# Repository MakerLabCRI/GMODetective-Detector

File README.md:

# GMODetective-Detector

DIY fluorescence detector for the [GMO Detective project](https://gmodetective.com/)

## BOM

8x C503B-BAN-CZ0A0451 [mouser](https://www.mouser.fr/ProductDetail/Cree-Inc/C503B-BAN-CZ0A0451?qs=%2Fha2pyFaduidizlAeORLOPChSupn8qVQ9Kn4bl13zJ7nUG9%252B2UeDbT0K%252B9FgAF1f)

8x 68 ohm resistor [mouser](https://www.mouser.fr/ProductDetail/Yageo/CFR-25JT-52-68R?qs=%2Fha2pyFaduip15hodXcAQzG82qC8UTcP%2FVcFQd8KsgKmaA7VFXCJAQ%3D%3D)

1x 10uF electrolytic capacitor [mouser](https://www.mouser.fr/ProductDetail/Panasonic/ECA-1JM100B?qs=%2Fha2pyFadugf96c9oovEvKSc4mhyX5s0jUH4ND99LTDADYv5TkhqzA%3D%3D)

1x Fuse 500ma RXEF050 [mouser](https://www.mouser.fr/ProductDetail/Littelfuse/RXEF050?qs=k5V78Jg%2Feq7BserVMEB6DA%3D%3D)

1x micro USB 2P with 90° pins [Taobao](https://item.taobao.com/item.htm?spm=a230r.1.14.68.312b6bc3MnUb4G&id=597273597165&ns=1&abbucket=19#detail)
[Aliexpress](https://fr.aliexpress.com/item/4000049679173.html?spm=a2g0o.productlist.0.0.6fd1f912MCE4d2&algo_pvid=a3873bf6-c53e-42d9-8363-89ecb1d975f8&algo_expid=a3873bf6-c53e-42d9-8363-89ecb1d975f8-4&btsid=0b0a182b16071189178941562e2389&ws_ab_test=searchweb0_0,searchweb201602_,searchweb201603)
[Aliexpress (90 ° version color B or D)](https://aliexpress.com/item/4001293555150.html)
[Aliexpress (90° version color A or C)](https://fr.aliexpress.com/item/1005001515820458.html)

## 3D Model of PCB

## 3d printable frame

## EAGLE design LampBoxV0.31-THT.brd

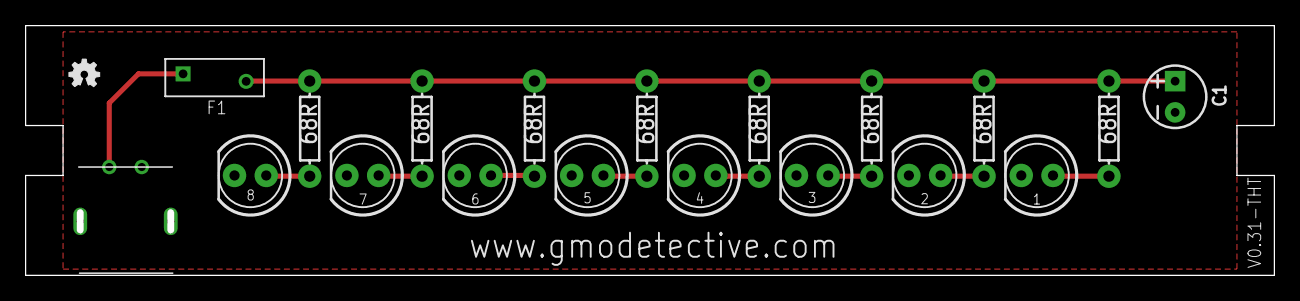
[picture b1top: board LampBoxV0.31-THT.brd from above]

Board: 2 copper layers, 100.0 x 20.0 mm, 22 parts (1 on the bottom side), 11 nets.

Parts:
1, 2, 3, 4, 5, 6, 7, 8: LED_5MM
C1: 10UF-POLARGMODETECTOR; CPOL-RADIAL-2.5MM-5MM
F1: LITTELFUSE_RXEF050LITTELFUSE_RXEF050_0_0; LITTELFUSE_RXEF050_0
LOGO1: OSHW-LOGOMINI; OSHW-LOGO-MINI
R1, R2, R3, R4, R5, R6, R7, R8: 68R; AXIAL-0.3
U$2: LOGO_GMO_DETECTIVENEW; LOGO_GMO_DETECTIVE
U$3: LOGO-CRI-NEW-110MM-BOTTOM-SILK; LOGO_CRI-NEW-BMP10MM-BOTTOM
U$4: USB-2P; MICRO-USB2P-TB1

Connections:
+5V: C1.1, F1.2, R1.P$1, R2.P$1, R3.P$1, R4.P$1, R5.P$1, R6.P$1, R7.P$1, R8.P$1
GND: 1.K, 2.K, 3.K, 4.K, 5.K, 6.K, 7.K, 8.K, C1.2, U$4.GND
unnamed: 1.A, R1.P$2
unnamed: 2.A, R2.P$2
unnamed: 3.A, R3.P$2
unnamed: 4.A, R4.P$2
unnamed: 5.A, R5.P$2
unnamed: 6.A, R6.P$2
unnamed: 7.A, R7.P$2
unnamed: 8.A, R8.P$2
VIN: F1.1, U$4.5V

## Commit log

2020-12-04 added eagle files
2020-12-04 updated pcb files and readme
2020-12-05 cosmetic improvements
2020-12-05 added PDFs
2020-12-05 resized img
2020-12-05 updated img
2020-12-09 updated repi structure
2020-12-23 openscad code
2021-10-21 adding dusjagr's modded version for 3d printing
2021-10-21 cleaning some files
2021-11-15 thinner sidewalls
2021-11-15 minor change to readme
2021-11-15 v04 of 3dprintable reader, fixed
2025-05-27 STL and new design
2025-06-22 STL and new design 2

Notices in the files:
parts and their libraries:
SparkFun-Aesthetics: Licensing: Creative Commons ShareAlike 4.0 International - https://creativecommons.org/licenses/by-sa/4.0
